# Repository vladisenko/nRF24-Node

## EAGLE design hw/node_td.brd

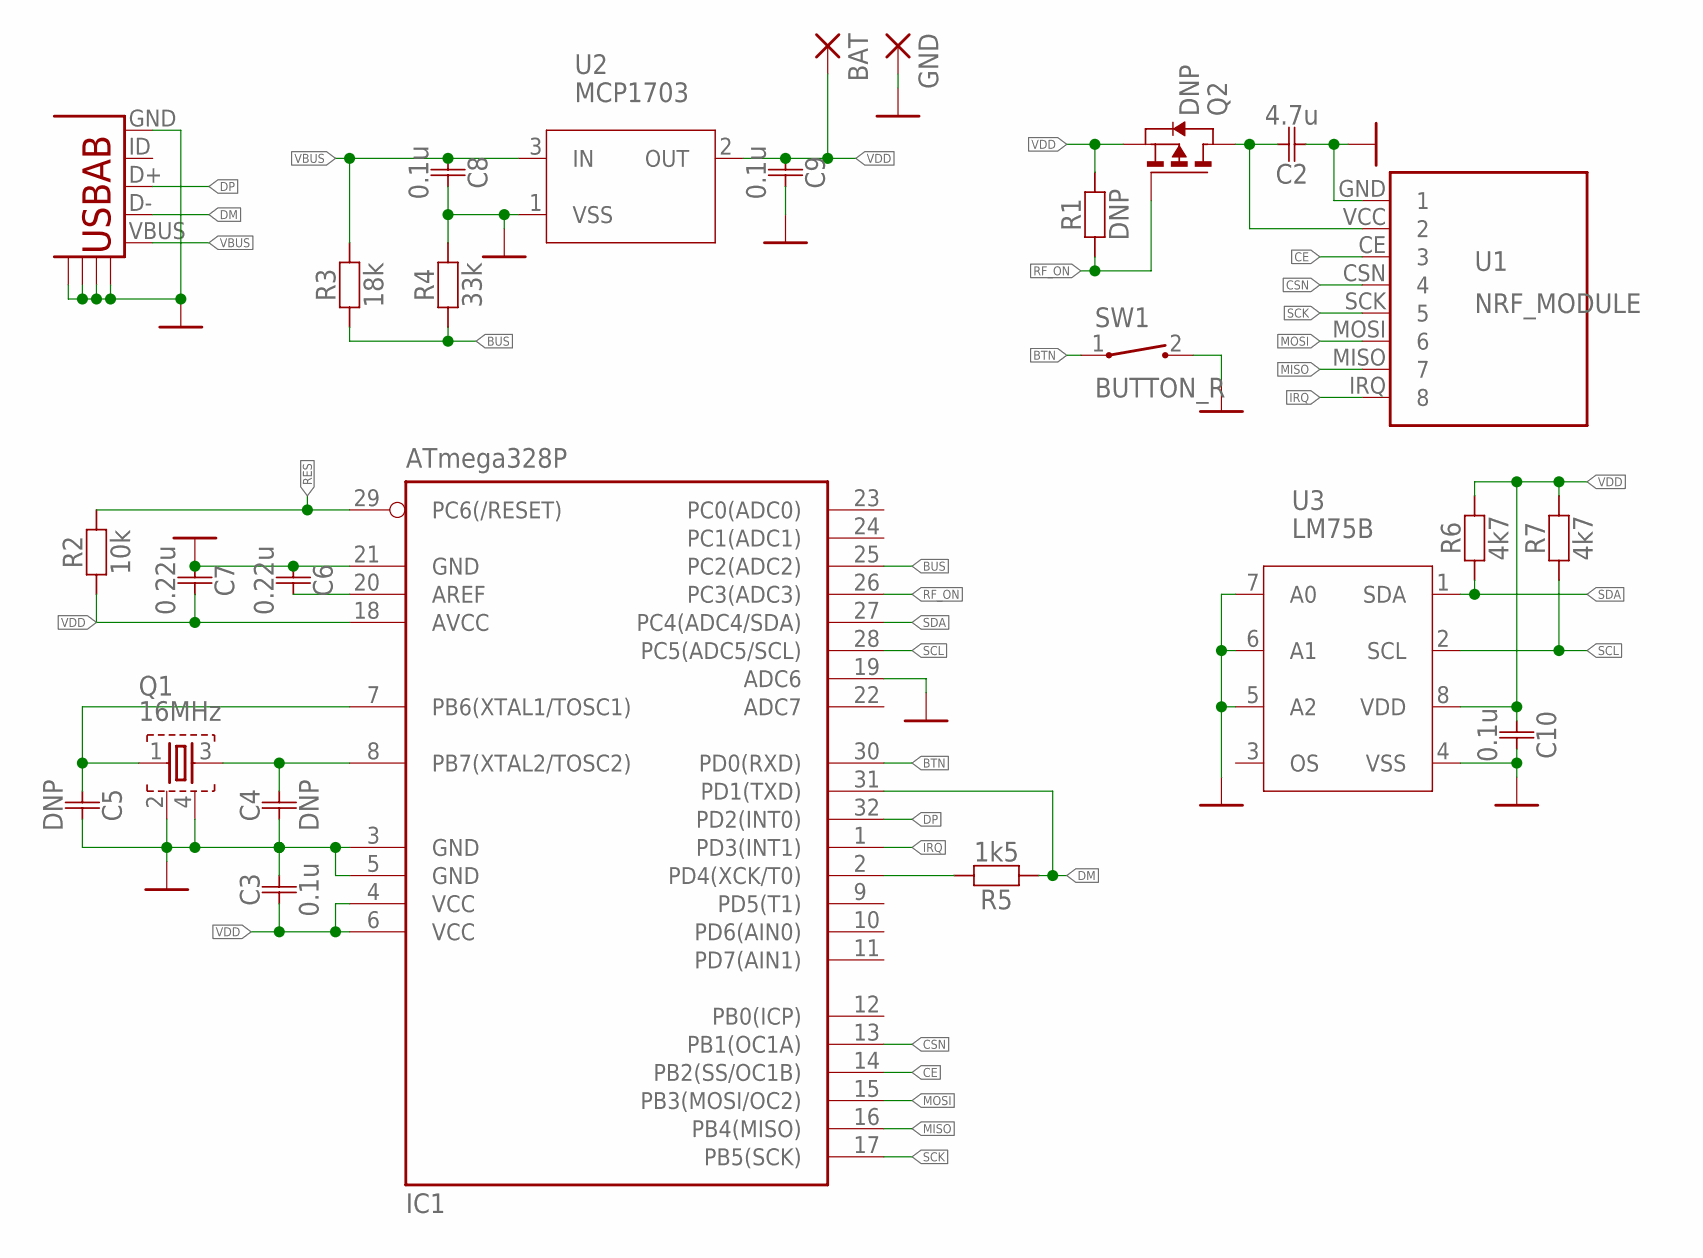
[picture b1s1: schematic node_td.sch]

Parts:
BAT: WIREPAD1,6/0,9; 1,6/0,9
C2: 4.7u; 0805
C3, C8, C9, C10: 0.1u; 0402
C4, C5: DNP; 0402
C6, C7: 0.22u; 0402
GND: WIREPAD1,6/0,9; 1,6/0,9
IC1: ATmega328P; TQFP32-08
Q1: 16MHz; FA-20H
Q2: DNP; SOT23
R1: DNP; 0402
R2: 10k; 0402
R3: 18k; 0402
R4: 33k; 0402
R5: 1k5; 0402
R6, R7: 4k7; 0402
SW1: BUTTON_R; BUTTON_1
U1: NRF_MODULE
U2: MCP1703; SOT23
U3: LM75B; MSOP8
U$1: UNTITLED_USB_AB; USB-MICRO-MOD

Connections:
BTN: IC1.30 (PD0(RXD)), SW1.1
BUS: IC1.25 (PC2(ADC2)), R3.P$1, R4.P$1
CE: IC1.14 (PB2(SS/OC1B)), U1.CE (3)
CSN: IC1.13 (PB1(OC1A)), U1.CSN (4)
DM: IC1.31 (PD1(TXD)), R5.P$1, U$1.D-
DP: IC1.32 (PD2(INT0)), U$1.D+
GND: C2.P$1, C3.P$2, C4.P$1, C5.P$2, C6.P$1, C7.P$1, C8.P$2, C9.P$2, C10.P$2, GND.1, IC1.3 (GND), IC1.5 (GND), IC1.19 (ADC6), IC1.21 (GND), Q1.2, Q1.4, R4.P$2, SW1.2, U1.GND (1), U2.1 (VSS), U3.4 (VSS), U3.5 (A2), U3.6 (A1), U3.7 (A0), U$1.GND, U$1.GND@1, U$1.GND@2, U$1.GND@3, U$1.GND@4
IRQ: IC1.1 (PD3(INT1)), U1.IRQ (8)
MISO: IC1.16 (PB4(MISO)), U1.MISO (7)
MOSI: IC1.15 (PB3(MOSI/OC2)), U1.MOSI (6)
unnamed: IC1.2 (PD4(XCK/T0)), R5.P$2
unnamed: C6.P$2, IC1.20 (AREF)
unnamed: C5.P$1, IC1.7 (PB6(XTAL1/TOSC1)), Q1.1
unnamed: C4.P$2, IC1.8 (PB7(XTAL2/TOSC2)), Q1.3
unnamed: C2.P$2, Q2.3 (D), U1.VCC (2)
RES: IC1.29 (PC6(/RESET)), R2.P$2
RF_ON: IC1.26 (PC3(ADC3)), Q2.1 (G), R1.P$1
SCK: IC1.17 (PB5(SCK)), U1.SCK (5)
SCL: IC1.28 (PC5(ADC5/SCL)), R7.P$1, U3.2 (SCL)
SDA: IC1.27 (PC4(ADC4/SDA)), R6.P$1, U3.1 (SDA)
VBUS: C8.P$1, R3.P$2, U2.3 (IN), U$1.VBUS
VDD: BAT.1, C3.P$1, C7.P$2, C9.P$1, C10.P$1, IC1.4 (VCC), IC1.6 (VCC), IC1.18 (AVCC), Q2.2 (S), R1.P$2, R2.P$1, R6.P$2, R7.P$2, U2.2 (OUT), U3.8 (VDD)

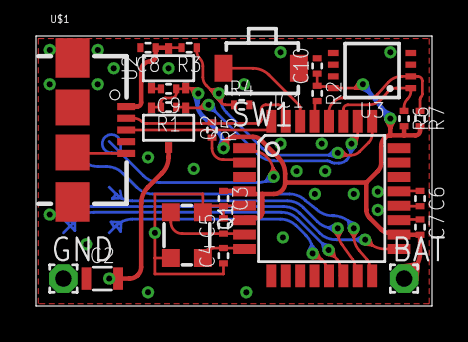
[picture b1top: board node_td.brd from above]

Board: 2 copper layers, 22.0 x 15.0 mm, 26 parts (1 on the bottom side), 22 nets.

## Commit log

2016-05-24 :octocat: Added .gitattributes & .gitignore files
2016-05-24 add hw and bootloader
2016-05-24 add pics
